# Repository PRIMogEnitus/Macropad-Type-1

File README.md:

# Macropad
 
 Simple 11 keys macropad suitable made using KiCad 7 and some schematic and footprint libraries.
 
CURRENTLY UNTESTED!

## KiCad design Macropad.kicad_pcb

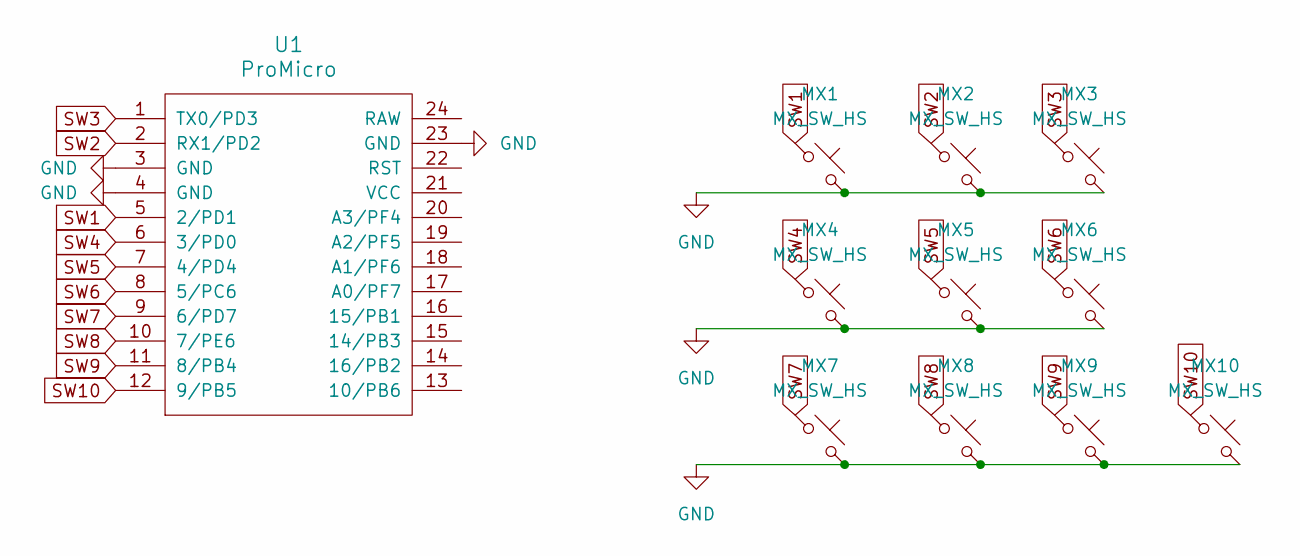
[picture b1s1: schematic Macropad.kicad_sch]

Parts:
MX1, MX2, MX3, MX4, MX5, MX6, MX7, MX8, MX9, MX10: MX_SW_HS; SW_MX_HS_1u
U1: ProMicro; ArduinoProMicro

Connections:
GND: MX1.2, MX2.2, MX3.2, MX4.2, MX5.2, MX6.2, MX7.2, MX8.2, MX9.2, MX10.2, U1.3 (GND), U1.4 (GND), U1.23 (GND)
SW1: MX1.1, U1.5 (2/PD1)
SW2: MX2.1, U1.2 (RX1/PD2)
SW3: MX3.1, U1.1 (TX0/PD3)
SW4: MX4.1, U1.6 (3/PD0)
SW5: MX5.1, U1.7 (4/PD4)
SW6: MX6.1, U1.8 (5/PC6)
SW7: MX7.1, U1.9 (6/PD7)
SW8: MX8.1, U1.10 (7/PE6)
SW9: MX9.1, U1.11 (8/PB4)
SW10: MX10.1, U1.12 (9/PB5)

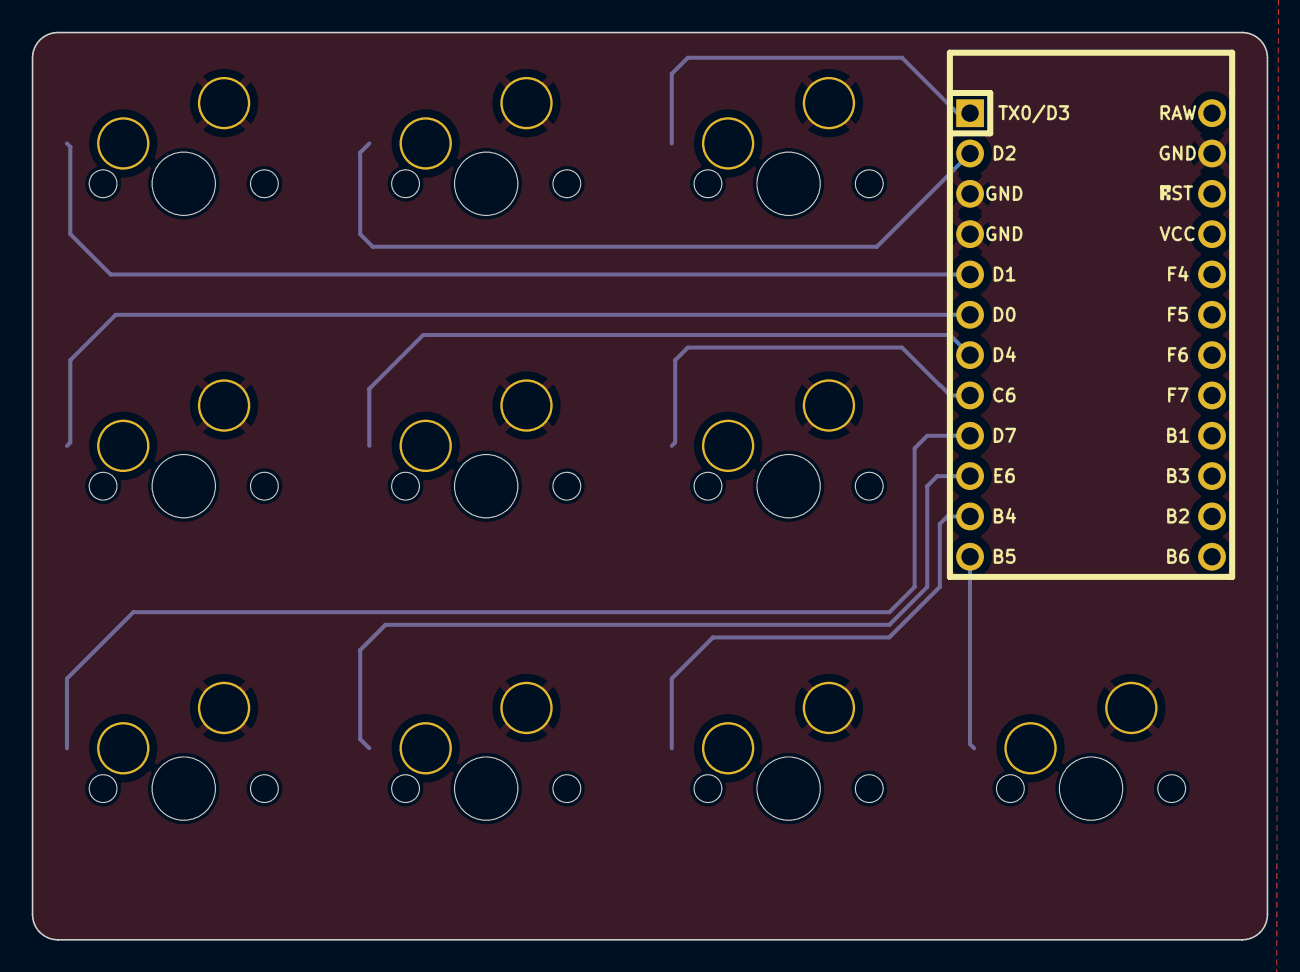
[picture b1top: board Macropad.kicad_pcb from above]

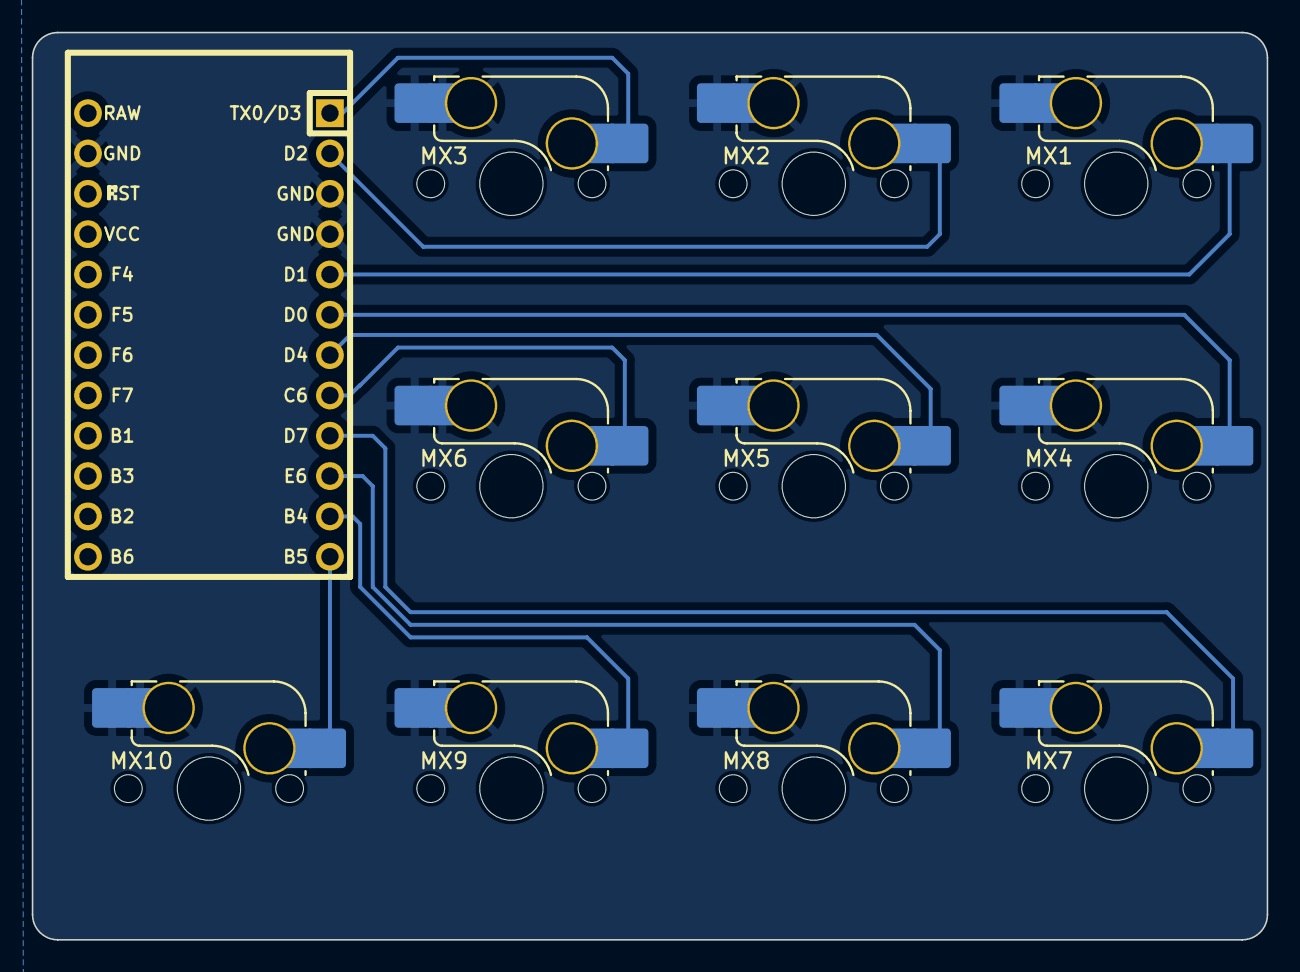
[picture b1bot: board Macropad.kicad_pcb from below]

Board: 2 copper layers, 77.8 x 57.2 mm, 11 parts (10 on the bottom side), 11 nets.

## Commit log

2023-06-14 Add Submodules
2023-06-14 Finished project
    13:09 14/6/2023 Wednesday.
    Macropad project finished.
2023-06-14 Updated gerber files
2023-06-14 Remove submodules
